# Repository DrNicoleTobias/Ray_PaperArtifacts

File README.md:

# Ray Sensor Documentation Notes

Ray is a batteryless, doorframe/passageway-mounted room-level occupancy monitoring sensor that uses changes in indoor ambient light reflections to detect people entering and exiting a room or hallway and estimate their direction of travel.

<table style="width: 100%; border-collapse: collapse;">
  <tr>
    <td style="width: 100%; text-align: center;">
      
      <br>
      <strong>Ray Use Scenario/Concept</strong>
    </td>
  </tr>
</table>

In this document, we provide the abstract of the work with highlights from our experiments, comments for the JSys reviewers, a layout of the folder/file structure, and instructions on how to build a Ray sensor and set it and a base station up for deployment.

# Abstract
Room-level occupancy-tracking systems enable intelligent control of building functions like air conditioning and power delivery to adapt to the needs of their occupants. Unfortunately, existing occupancy-tracking systems are bulky, have short battery lifetimes, are not privacy-preserving, or only provide coarse-grain occupancy information. Furthermore, retrofitting existing infrastructure with wired sensors is prohibitively expensive.

In this paper, we present Ray, a batteryless, doorframe/passageway-mounted room-level occupancy monitoring sensor that uses changes in indoor ambient light reflections to detect people entering and exiting a room or hallway and estimate direction of travel. We evaluated Ray in mixed lighting conditions on both sides of the doorway in an office-style setting, using subjects with a wide variety of physical characteristics. We conducted 881 controlled experiments in 7 doorways with 9 individuals and achieved a total detection accuracy of 100% and movement direction accuracy averaging 96.4%. Furthermore, we deployed Ray sensors for 64 days in 5 locations, comparing them with a commercial batteryless occupancy sensor. Ray outperformed the commercial sensor, particularly where traffic is moderate to heavy. Ray demonstrates that ambient light reflections provide both a promising low-cost, long-term sustainable option for monitoring how people use buildings and an exciting new research direction for batteryless computing.

# Artifact Evaluation - For JSys Reviewers
The artifacts associated with this paper consist of both hardware and software for building a functioning deployment of the Ray sensor.

We are including the custom PCB designs, Bill of Materials, and 3D prototype housing files used to create a Ray sensor. PDFs of the schematic and Design files are also included for reviewer convenience. Software for training and the firmware that runs the Ray sensor and base station are also provided. Documentation includes how to build, set up, tune, train, and deploy a Ray sensor as well as how to set up a base station for receiving the sensor data.

As the claims of this work are of the effectiveness of our custom Ray sensor, it is hard to automate items for testing and evaluation without actually having a physical sensor built, trained, and deployed for reviewers to test. After speaking with the chair of the Artifact Evaluation Board, we determined the best way to demonstrate the usability and reproducibility of this work is by providing the design files (raw and as PDFs for convenience), and making several demonstration videos to show the system working in controlled scenarios, in the presence of confounding cases, and when comparing to a commercial occupancy sensor. We hope they allow enough insight to judge the effectiveness, claims, and reproducibility of the work as it is hard to exactly recreate some of these experiments as they were gathered from live individuals walking through passageways.

# Folder/File Layout
This repo stores code, hardware files, and other technical documents for the project. Subdirectories are described below:

## Hardware
This folder contains all of the custom PCB Eagle design files (PDFs of the schematic and board design files are also included for reviewer convenience), Bill of Materials (BOM), and 3D prototype housing/enclosures files used to create a Ray sensor.

## Review_Material
This folder contains some of the additional artifact information for the working sensor including a Video Demo (.mp4) and a sampling of the data collected from both the controlled and uncontrolled experiments of the paper.  The Video Demo showcases the Ray sensor operating during a range of activities. These include people walking through doorways under the sensor, pass-by events where a person walks near the sensor but does not pass under it, and confounding cases like lingering and many people walking in a tight group. We also demonstrate in the video a comparison between the  sensor and the commercially available EnOcean sensor (a batteryless PIR-based occupancy sensor), showing that Ray is able to more accurately estimate the number of people during higher traffic conditions. 

Due to the nature of this project, much of the data gathering and ground truth labeling required manual intervention and processing to account for the amount of corner cases and fuzzy timing between two different sensors and ground truth.  A sampling of the manual data gathering for the controlled and uncontrolled experiments has been provided and the resulting excel files for the uncontrolled experiments are provided for review.  There are no scripts to run, table data for the uncontrolled experiments (Tables 5 and 6) came directly from excel formulas in the excel files for each location.

## Software
All software provided is either C code compiled and run on the MSP430FR5994 chips used for our sensor and base station or Python3 scripting code that is processed on a base station or laptop. Because there are variations in component quality and in doorway and lighting conditions, users want to train the classifier model on data more closely related to the test environment to improve accuracy. In that event, The following subfolders contain the code needed to gather the raw features from a Ray sensor (0_Get_Features) and train a new decision tree classifier model using those features (1_Train_Model). Once trained, the model will need to be manually implemented in the experiment code subfolders 2_Controlled_Studies and 3_Uncontrolled_Studies (specific locations to change are mentioned in those folders' ReadMe documentation.

### 0_Get_Features
This folder contains the firmware for both the Ray sensor and for a base station for gathering raw training data. The data gathered by the base station and sensor firmware here is intended for training a supervised classification model, in our case a decision tree model. This model should capture directional information from many individual events of common in and out events and can also include some additional example training data for some confounding, yet common, cases such as pass-by events. Have sample subjects walk in and out in a controlled manner to capture what the raw features from the sensor look like under local lighting conditions and environment. Collect this data using what is received at the base station and the result for that data that you wish to train with in a CSV file for use in training the model in the next step.

### 1_Train_Model
This folder contains a Python script called makedecisions.py that will use the CSV file of data gathered from the 0_Get_Features scripts/code in order to train a new decision tree to update the models for testing or real world deployment.

### 2_Controlled_Studies
This folder contains the firmware for both the Ray sensor and for a base station to receive packets from a Ray Sensor using the CC1101 Radio with a MSP430FR994 LaunchPad where the Ray Sensor sends a single packet for individual controlled events.

### 3_Uncontrolled_Studies
This folder contains the firmware for both the Ray sensor and for a base station to receive full packets from a deployed Ray Sensor using the CC1101 Radio with a MSP430FR994 LaunchPad where the Ray Sensor to send complete packets containing a sequence of 5 events, an estimate of their time between events, heartbeats in the absence of activity for 2 minutes, and history of the last two packets sent for redundancy.

# Building a Ray Sensor

In this section, we describe the steps it takes to build a physical Ray Sensor for deployment.

<table style="width: 150%; border-collapse: collapse;">
  <tr>
    <td style="width: 50%; text-align: center;">
      
      <br>
      <strong>Ray PCB Close Up</strong>
    </td>
    <td style="width: 100%; text-align: center;">
      
      <br>
      <strong>Ray Full Sensor</strong>
    </td>
  </tr>
</table>

## Housing/Enclosure, Parts, and Assembly
Our prototype hardware integrates a modular custom printed circuit board (PCB) housed in a 3D-printed plastic enclosure, four solar panels, and a TI CC1101 radio.

### Custom PCB
The PCB for the Ray sensor consists of three modular parts: a Solar_Module, a MCU_Module, and a Radio_Module. All design files for these modules and the Bill of Materials for all necessary PCB components can be found in the Hardware/PCB_Designs/ folder. Boards can be fabricated at many places online, such as OSHpark etc, and the components can be populated by hand or by a manufacturer as well. Design files can be viewed directly by a program like Eagle, but PDFs have been made available for convenience of viewing. The Solar_Module attaches to the MCU_Module and the MCU_Module attaches to the Radio_Module.

### 3D Enclosure
The 3D printed mounting system is made of PLA plastic and contains the PCB, solar cells, and necessary wiring connecting them. Enclosure designs to house the PCB and attach the solar panels to can be found in Hardware/3D_Enclosure/PCB_Housing_and_20_DegBody_Assembly.stl with a second file Hardware/3D_Enclosure/PCB_Housing_Cap.stl to make a cap to cover the PCB during deployment. The enclosure provides a nesting place for the solar cells, which angles the solar cell slots such that two of the four of the solar cells are pointed toward the entry, while the rest are pointed toward the exit.

### Connecting Solar Panels
Four solar panels need to be attached to the enclosure, where they will be divided into two sets of two panels each, one facing inward (the direction the radio antenna is pointing) and one set facing outward. The inward set of solar panels are connected in series and connected to the SOLAR1 terminal of the Solar Module PCB. The outward facing panels are also connected in series and then added to the SOLAR2 terminal.

### Tune the Detectors
Ray uses a detection circuit to determine when to wake up the microcontroller to assess the possible event. The detector circuitry is tunable using trim potentiometers (trim pots) pre-installation in deployment. Testers may find that, depending on the lighting conditions of a particular doorway, the sensitivity of the detector circuit's trim pots may need adjusting. We found in our experiments that we did need to adjust the trim pots some for the general lighting conditions and found that they generally worked for other similar lighting conditions without needing to be readjusted for every doorway. Using a screwdriver on TM1 for monitoring SOLAR1 or TM2 for monitoring SOLAR2 from the Solar_Module PCB schematics, turning to one direction will move the detection threshold and make the detectors more sensitive while turning in the opposite direction will make them less sensitive.

### Attaching a Radio
The Ray PCB also uses a TI CC1101 radio for communication that is to be connected to the Radio_Module in Hardware/PCB_Designs/. The TI CC1101 radio board is an off-the-shelf board that we designed a plug-in for on the Radio_Module boards. For our purposes, we considered the direction the antenna was pointing to be inward when mounting the sensor for practice, but one could train and adjust the code if pointing the other direction is preferred.

### Installing on a doorway
With all the parts assembled, tuned, connected, and attached to the 3D printed enclosure, the Ray sensor can be attached to the top of a doorway/passageway frame with solar panels facing down any preferred orientation. For our experiments, we affixed the 3D enclosure to a piece of wood with magnets screwed to the other side for ease in attaching and removing the sensor on different doorway/passageway frames, as most within our office building had metal frames or structures.

## Setting up a Base Station
To receive the data packets from the Ray Sensor, you will need a MSP430FR5994 LaunchPad and another off-the-shelf CC1101 Radio.  The radio will need to be connected to the LaunchPad’s pins as follows:
```
	*MSP430FR5994*	←    *CC1101*
		VCC	←	VCC
	 	GND	←	GND
	 	P3.4	←	GDO0
	 	P3.6	←	GDO2
	 	P4.3  	←	CSN
	 	P5.0  	←	MOSI
	 	P5.1 	←	MISO
	 	P5.2  	←	SCK 
```
And as documented in the top comment of each basestation_receive.c code in the folders containing base station code. If these pins need to be modified for a particular setup, there is an /includes/pins.h file in each folder containing base station code that can be easily modified.  Once attached, the base station firmware will need to be installed to the LaunchPad simply by connecting the LaunchPad by USB to a computer with msp-gcc installed.  Navigate to the firmware folder of interest, update the makefile as suggested in that folder’s readme, and then simply run “make install” to install the firmware on the LaunchPad.   Data can be gathered by simply reading off what is sent over serial or by using a script that grabs what is coming across from the LaunchPad over serial to a database.

## Training the event classification model
### Gather Raw Feature Data
All code needed to gather features to train a new model is located in the /Software/0_Get_Features/ folder for both the base station and the sensor.  Connect the LaunchPad to install the sensors firmware using the on board programmer (requires removing some jumpers) then return the jumpers and install the base station firmware for data collection.  Attach the sensor to a doorway or passageway face down, orientated in the direction you wish to train as inward vs outward.  Gather the data sent from the sensor to the base station over the serial port from many different individual controlled events and denote the ground truth for supervised training.  Record all of this data in a CSV file that will be used to train a new decision tree model.

### Train Model
To train a new decision for a new deployable environment, the following Python3 libraries must be installed: pandas, graphviz, and scikit-learn.  Once installed, navigate to the Software/1_Train_Model/ folder and locate the makedecisions.py file.  The file will need an updated path to the CSV feature data that was collected and there are several different classifier options available to train with.  Simply run “python3 makedecisions.py” to execute that code.  A visual graph will be generated for you to assess just how the training data falls in the model.
Some sample training data is available in that folder from our experimental setup that can be run with the makedecisions.py script in its current state to test how that script works.

### Translate Decision Tree Diagram to Implementation**
Now that a tree has been generated by the makedecisions.py script and the training data gathered, it will need to be manually translated and implemented in the deployable code for evaluating_event() found in both 2_Controlled_Experiments/RaySensor/SensorControlExperiments.c and 3_Uncontrolled_Experiments/RaySensor/SensorControlExperiments.c.  The documentation in both places will reference the line numbers where that function resides.  Once implemented, the firmware can be installed/uploaded to the sensor and the sensor can be deployed.

### Installing Firmware
The Ray firmware is designed to be ultra-low power, even in active mode, and has low computational complexity, offloading the bulk of the detection to the hardware circuits. All firmware code in the Software folder basically requires the same setup in order to program either the launchpad or the Ray Sensor.
1. Change the SUPPORT_FILE_DIRECTORY in the makefile to your msp430 gcc include
   path.
2. Hook up a MSP430FR5994 LaunchPad to your computer.
3. Connect the sensor to the Programmer pins on the LaunchPad (some jumpers may need to be removed to accomplish this) and plug them in to the appropriate programming pins on the MCU_Module.
4. Use "make install" to load the program into your device.
5. Detach from the programmer and reconnect the PCB in the enclosure and the unit is ready to be deployed. (Skip steps 3 and 5 if programming a MSP430 LaunchPad for a base station)

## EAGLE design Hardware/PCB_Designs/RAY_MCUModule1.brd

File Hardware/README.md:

This folder contains all PCB hardware module files, Bill of Materials (BOM) associated with each module and the design files to 3D print a prototyping enclosure and cap/cover for the finished sensor PCB.

# PCB_Designs
This folder contains all of the design files for the custom Ray PCB modules (Solar, MCU, and Radio) as well as PDFs of these design files for viewers convenience.  These files were created using the AutoDesk Eagle Software.

# 3D_Enclosure
This folder is for the various 3D housing models that have been created for housing the custom PCB and solar panels for the final Ray Sensor.  

**BOM.xlsx**
This is the Bill of Materials that lists the parts/components used for each of the custom PCB modules (arranged by tabs).

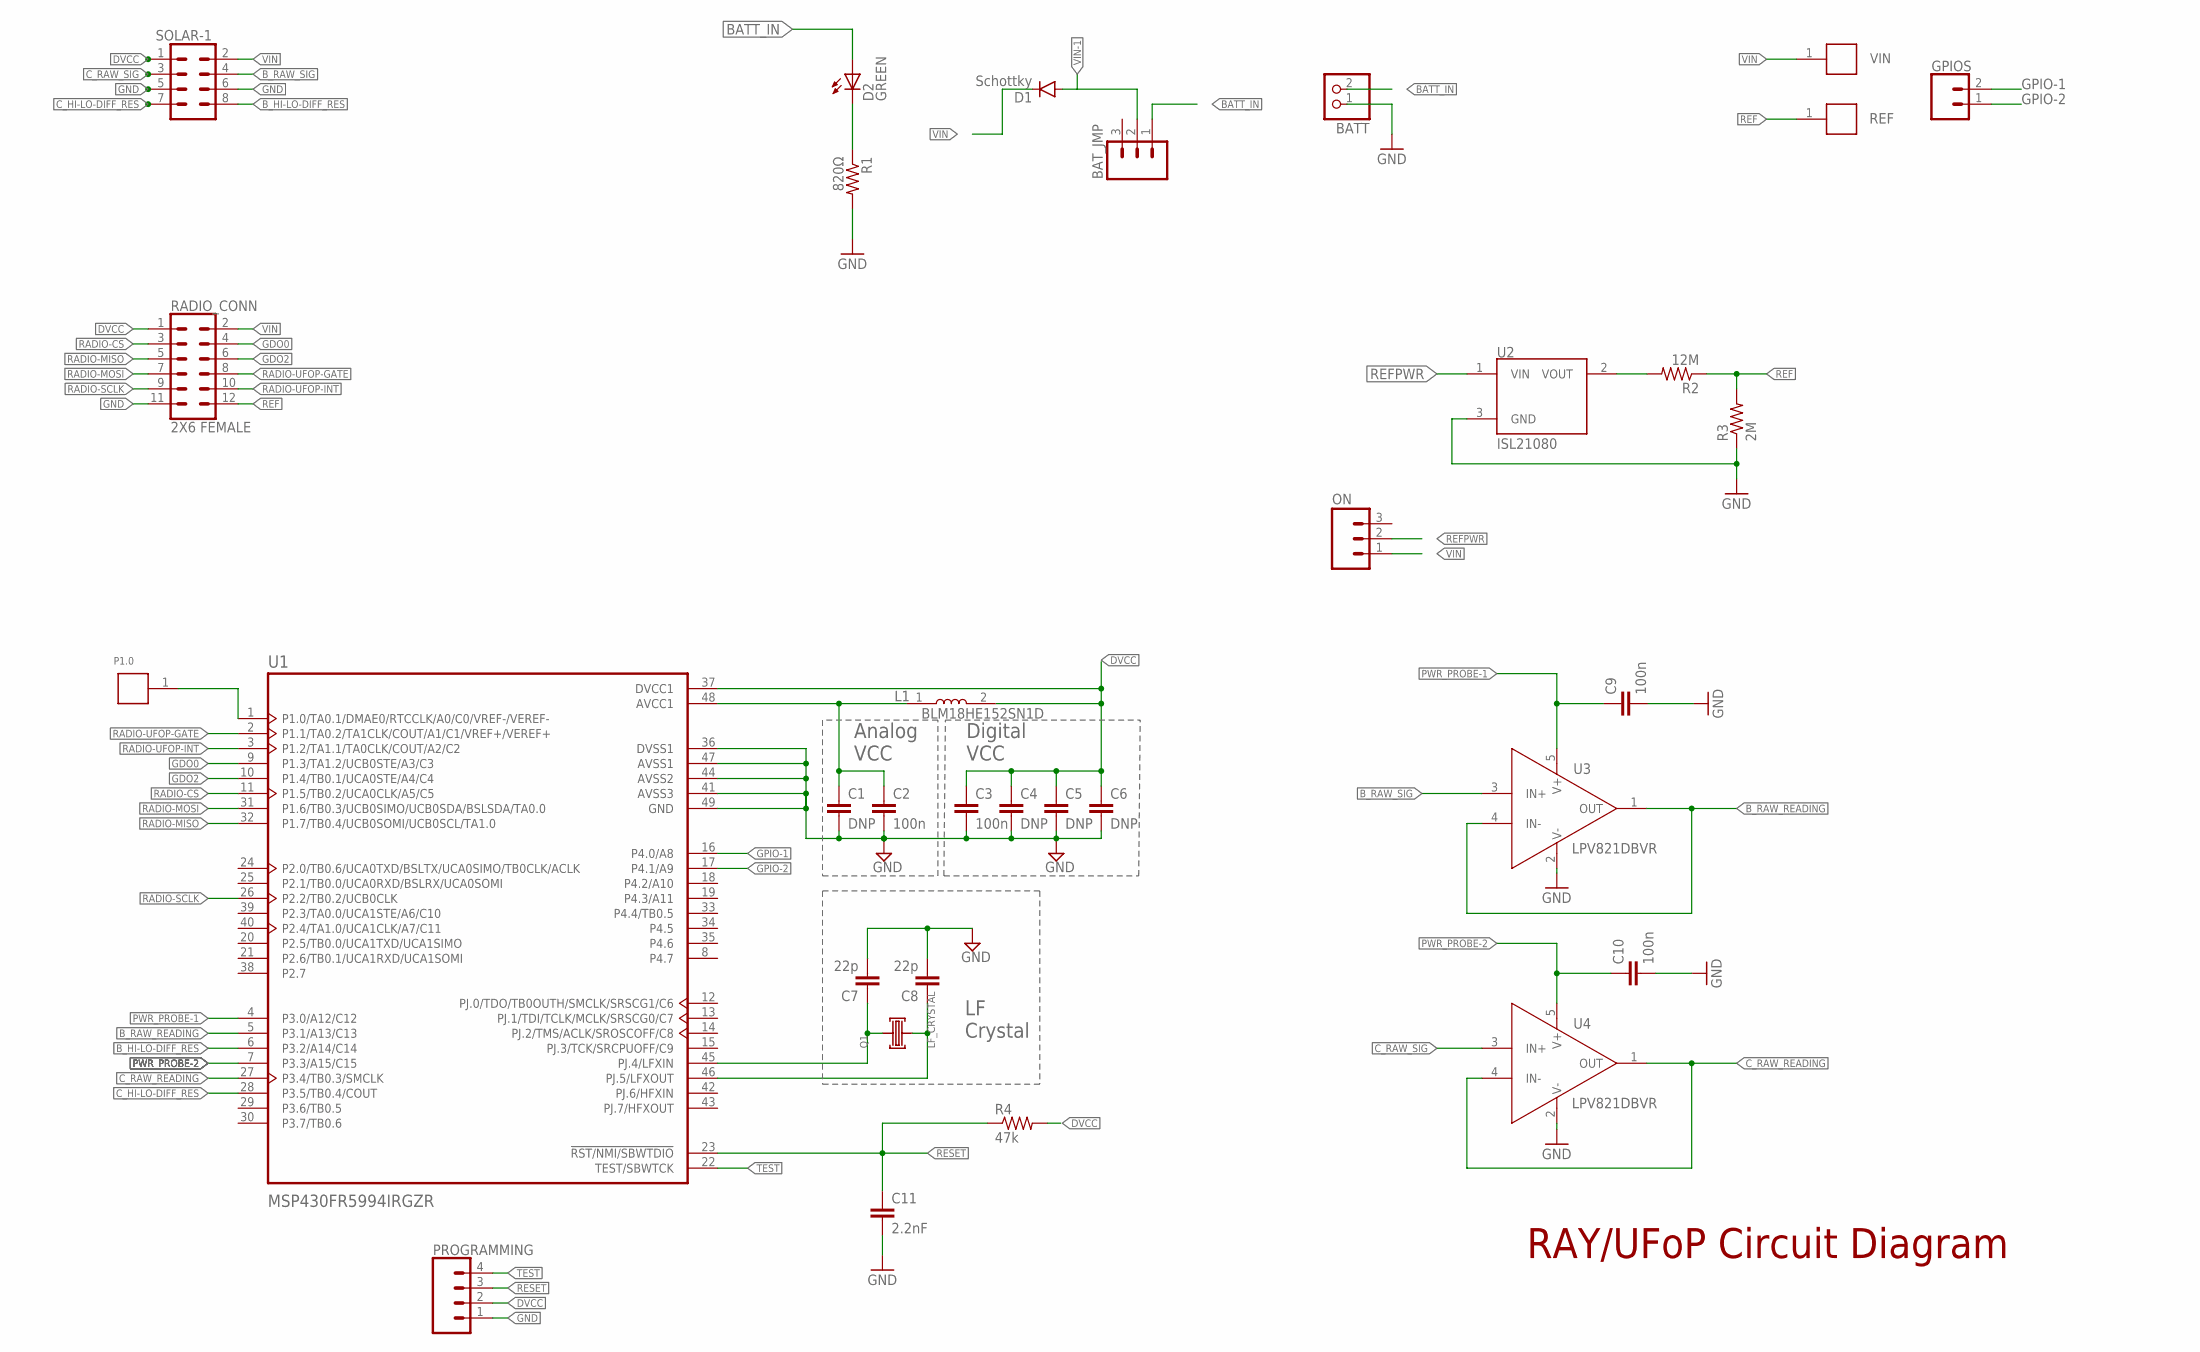
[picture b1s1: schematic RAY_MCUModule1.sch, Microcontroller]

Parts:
BATT: PINHD-1X2; 1X02
BAT_JMP: M03; 1X03-1.27MM
C1, C4, C5, C6: DNP; C0603
C2, C3, C9, C10: 100n; C0603
C7, C8: 22p; C0603
C11: 2.2nF; C0603
D1: Schottky; SOD523
D2: GREEN; CHIP-LED0805
GPIOS: CONN_02; 1X02
L1: BLM18HE152SN1D; INDC1608X95
ON: M03; 1X03-1.27MM
P1.0: RCU-0C; TE_RCU-0C
PROGRAMMING: CONN_04; 1X04
Q1: LF_CRYSTAL
R1: 820Ω; 0603-RES
R2: 12M; 0603-RES; DIGIKEY 541-6.20MHCT-ND
R3: 2M; 0603-RES; DIGIKEY 311-1.00MHRCT-ND
R4: 47k; 0603-RES; DIGIKEY 311-1.00MHRCT-ND
RADIO_CONN: 2X6 FEMALE; 2X6
REF: RCU-0C; TE_RCU-0C
SOLAR-1: CONN_04X2; 2X4
U1: MSP430FR5994IRGZR; QFN50P700X700X100-49N
U2: ISL21080; SOT-23; DIGIKEY ISL21080DIH309Z-TKCT-ND
U3, U4: LPV821DBVR; SOT95P280X145-5N
VIN: RCU-0C; TE_RCU-0C

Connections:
AVCC: C1.1, C2.1, L1.1, U1.48 (AVCC1)
BATT_IN: BATT.2, BAT_JMP.1, D2.A
B_HI-LO-DIFF_RES: SOLAR-1.8, U1.6 (P3.2/A14/C14)
B_RAW_READING: U1.5 (P3.1/A13/C13), U3.1 (OUT), U3.4 (IN-)
B_RAW_SIG: SOLAR-1.4, U3.3 (IN+)
C_HI-LO-DIFF_RES: SOLAR-1.7, U1.28 (P3.5/TB0.4/COUT)
C_RAW_READING: U1.27 (P3.4/TB0.3/SMCLK), U4.1 (OUT), U4.4 (IN-)
C_RAW_SIG: SOLAR-1.3, U4.3 (IN+)
DVCC: C3.1, C4.1, C5.1, C6.1, L1.2, PROGRAMMING.2, R4.2, RADIO_CONN.1, SOLAR-1.1, U1.37 (DVCC1)
GDO0: RADIO_CONN.4, U1.9 (P1.3/TA1.2/UCB0STE/A3/C3)
GDO2: RADIO_CONN.6, U1.10 (P1.4/TB0.1/UCA0STE/A4/C4)
GND: BATT.1, C1.2, C2.2, C3.2, C4.2, C5.2, C6.2, C7.2, C8.2, C9.2, C10.2, C11.2, PROGRAMMING.1, R1.2, R3.1, RADIO_CONN.11, SOLAR-1.5, SOLAR-1.6, U1.36 (DVSS1), U1.41 (AVSS3), U1.44 (AVSS2), U1.47 (AVSS1), U1.49 (GND), U2.3 (GND), U3.2 (V-), U4.2 (V-)
GPIO-1: GPIOS.2, U1.16 (P4.0/A8)
GPIO-2: GPIOS.1, U1.17 (P4.1/A9)
unnamed: P1.0.1, U1.1 (P1.0/TA0.1/DMAE0/RTCCLK/A0/C0/VREF-/VER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)
unnamed: D2.C, R1.1
unnamed: R2.2, U2.2 (VOUT)
unnamed: C8.1, Q1.2, U1.46 (PJ.5/LFXOUT)
unnamed: C7.1, Q1.1, U1.45 (PJ.4/LFXIN)
PWR_PROBE-1: C9.1, U1.4 (P3.0/A12/C12), U3.5 (V+)
PWR_PROBE-2: C10.1, U1.7 (P3.3/A15/C15), U4.5 (V+)
RADIO-CS: RADIO_CONN.3, U1.11 (P1.5/TB0.2/UCA0CLK/A5/C5)
RADIO-MISO: RADIO_CONN.5, U1.32 (P1.7/TB0.4/UCB0SOMI/UCB0SCL/TA1.0)
RADIO-MOSI: RADIO_CONN.7, U1.31 (P1.6/TB0.3/UCB0SIMO/UCB0SDA/BSLSDA/TA0.0)
RADIO-SCLK: RADIO_CONN.9, U1.26 (P2.2/TB0.2/UCB0CLK)
RADIO-UFOP-GATE: RADIO_CONN.8, U1.2 (P1.1/TA0.2/TA1CLK/COUT/A1/C1/VREF+/VERE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)
RADIO-UFOP-INT: RADIO_CONN.10, U1.3 (P1.2/TA1.1/TA0CLK/COUT/A2/C2)
REF: R2.1, R3.2, RADIO_CONN.12, REF.1
REFPWR: ON.2, U2.1 (VIN)
RESET: C11.1, PROGRAMMING.3, R4.1, U1.23 (!RST/NMI/SBWTDIO)
TEST: PROGRAMMING.4, U1.22 (TEST/SBWTCK)
VIN: D1.C, ON.1, RADIO_CONN.2, SOLAR-1.2, VIN.1
VIN-1: BAT_JMP.2, D1.A

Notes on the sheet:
RAY/UFoP Circuit Diagram
Analog
VCC
Digital
Crystal

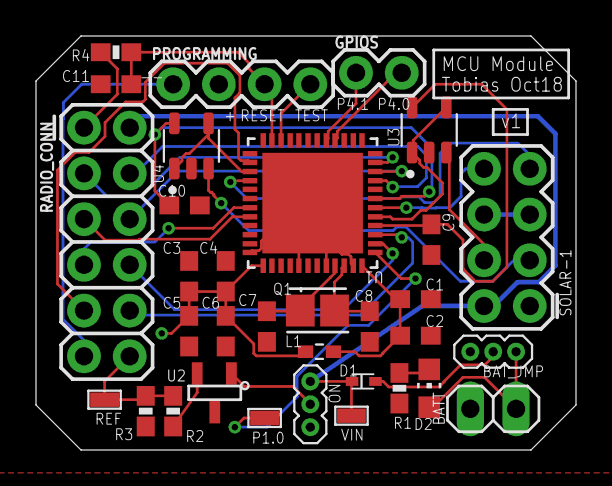
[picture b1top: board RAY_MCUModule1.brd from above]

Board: 2 copper layers, 30.0 x 23.0 mm, 33 parts (0 on the bottom side), 33 nets.

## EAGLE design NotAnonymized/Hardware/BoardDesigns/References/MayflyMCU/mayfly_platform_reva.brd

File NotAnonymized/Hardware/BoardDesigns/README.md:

This folder contains all of the various PCB design revisions and documentation over the life of this project.  
-->Note:  Documentation of Waldo hardware revisions only guaranteed complete starting with revision F.

# References
Various materials used by past hardware developers to create the base of this project's schematics

#Waldo Rev. A through #Waldo Rev. C
These folders contain past versions of the Waldo project and do not function as expected.  These are left for archival reasons as the project grows.

#Waldo Rev. D
Status:  Works kind-of.
This folder contained the closest working model of the PCB.  This PCB design, however, works as expected only when a Saleae is connected to the system at all test points as its internal resistance greatly influences the system and impacted resistor values chosen in the schematic.  

#Waldo Rev. E
Status:  Dead-end.
This folder contains an incomplete attempt at improving upon Rev. D.  Progress stalled on this attempt and ended with the graduation of a student.  

#Waldo Rev. F (NT)
Status:  Currently being developed/tested - Under construction.
This folder contains the version of Waldo's PCB design that is currently being developed.  Rather than branching from Rev. E, this was developed by a new student to the project to modify and address concerns that arose from Rev. D.  Rev. F is being developed with the assumption that a Saleae need not be attached for the system to function.  This folder contains all files and complete hardware documentation for the state of Rev. F.

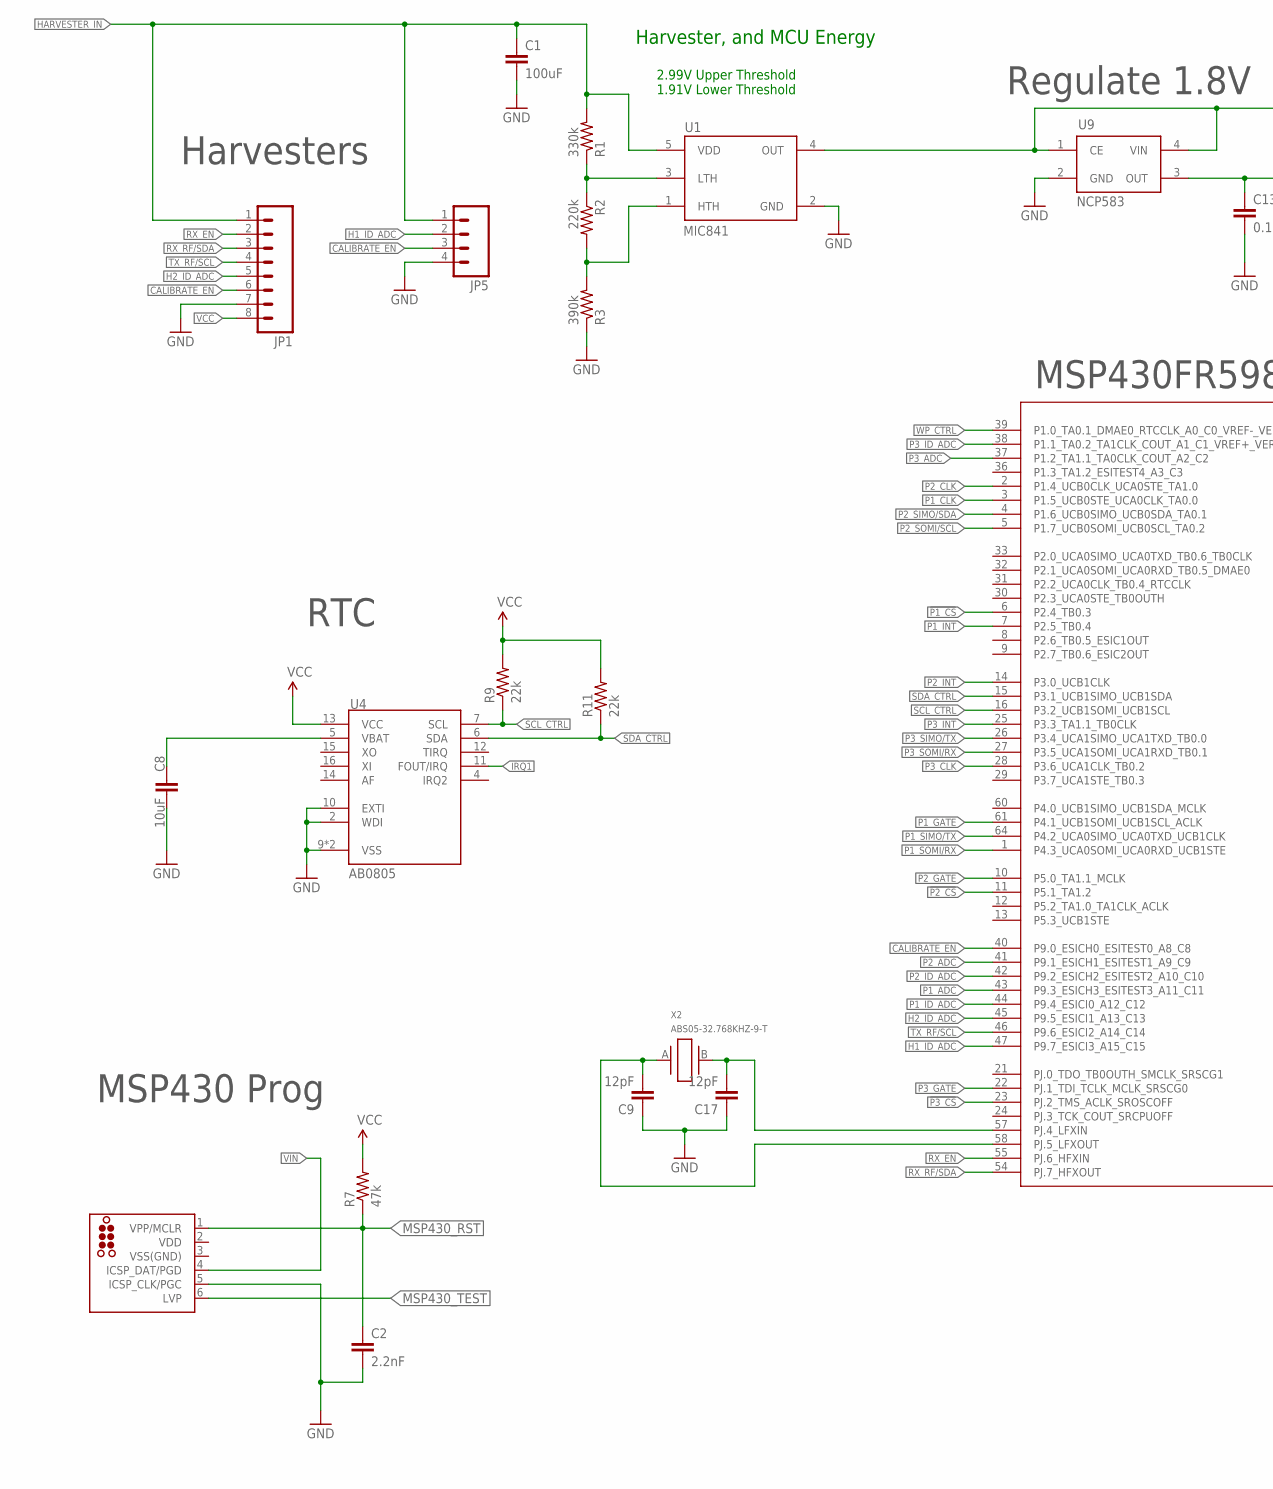
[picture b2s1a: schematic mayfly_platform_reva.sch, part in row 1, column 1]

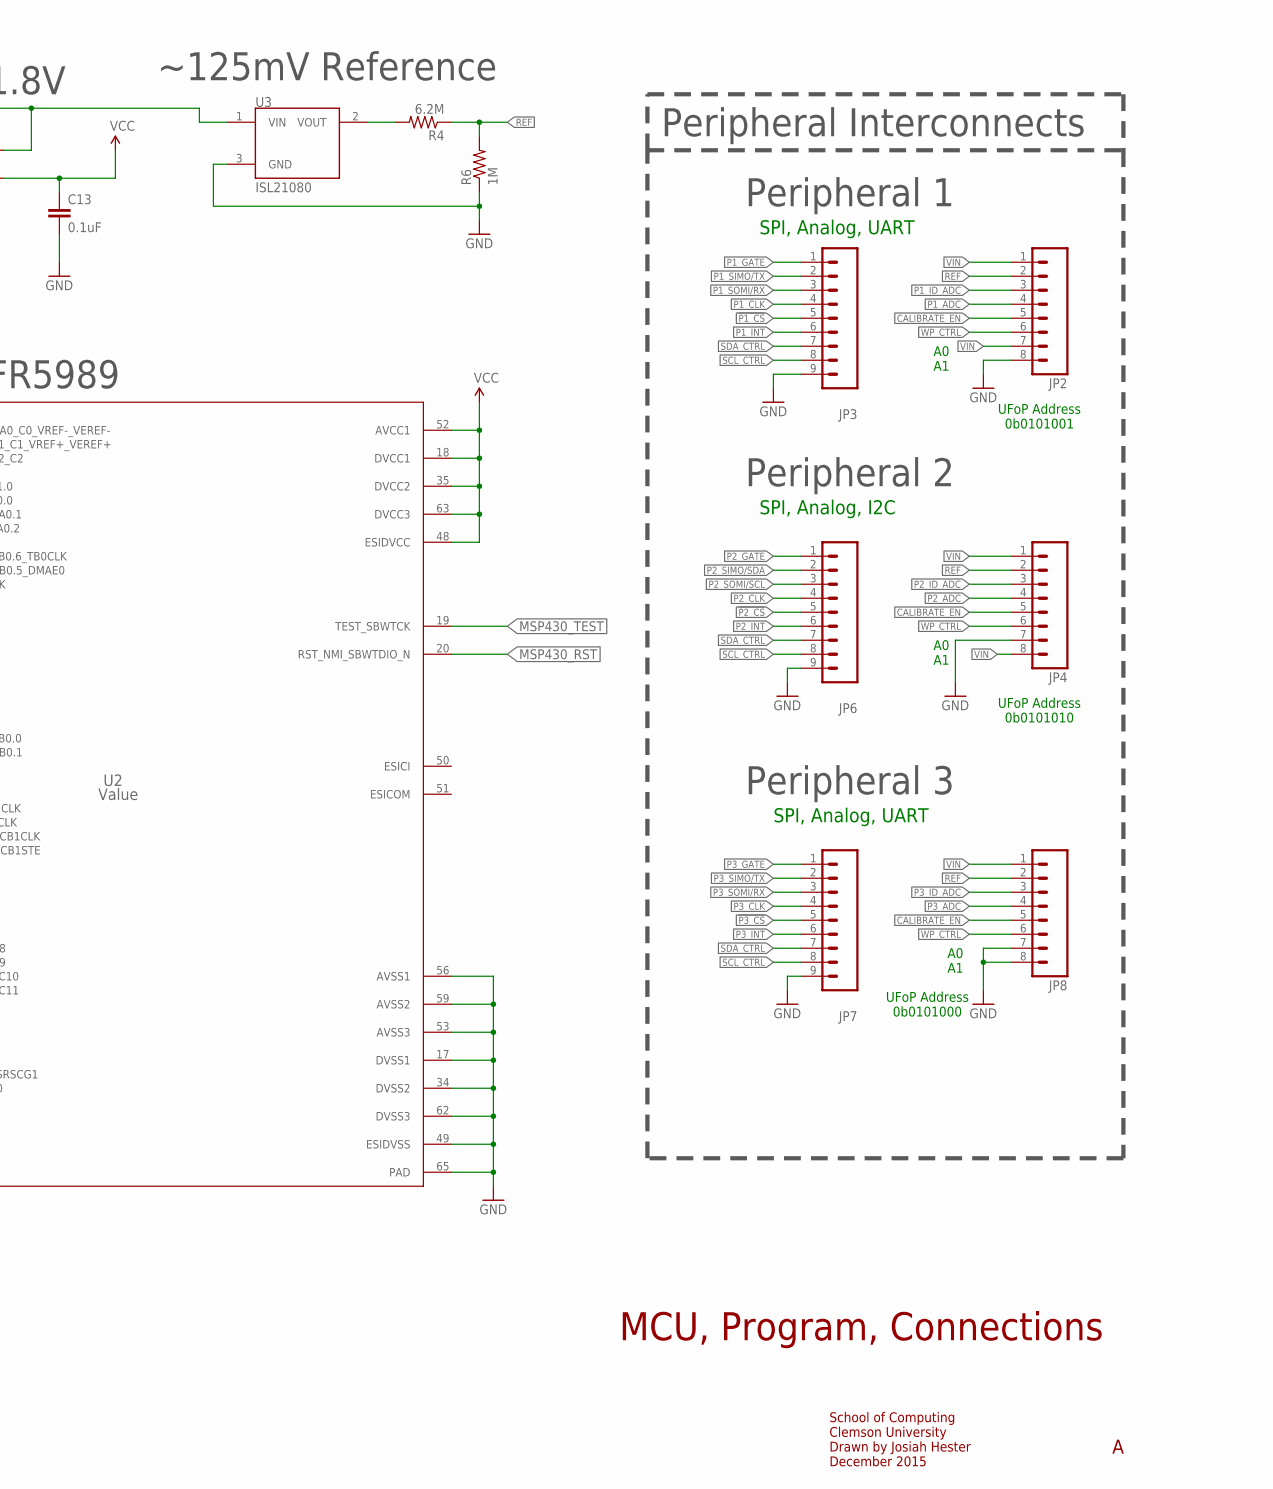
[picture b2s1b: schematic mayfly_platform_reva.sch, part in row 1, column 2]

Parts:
C1: 100uF; 1210; DIGIKEY 490-9969-1-ND
C2: 2.2nF; 0603
C8: 10uF; 0805
C9, C17: 12pF; 0603
C13: 0.1uF; 0603
J1: TC2030-MCP-NL
JP1, JP2: M081.27MM; 1X08-1.27MM; DIGIKEY S9014E-08-ND
JP3, JP6, JP7: M091.27MM; 1X09-1.27MM
JP4, JP8: M081.27MM; 1X08-1.27MM
JP5: M041.27MM; 1X04-1.27MM
R1: 330k; 0603; DIGIKEY 311-330KGRCT-ND
R2: 220k; 0603; DIGIKEY 311-220KGRCT-ND
R3: 390k; 0603; DIGIKEY 311-390KGRCT-ND
R4: 6.2M; 0603; DIGIKEY 541-6.20MHCT-ND
R6: 1M; 0603; DIGIKEY 311-1.00MHRCT-ND
R7: 47k; 0603
R9, R11: 22k; 0603
U1: MIC841; SC70-5; DIGIKEY 576-2923-1-ND
U2: Value; RGC0064B; DIGIKEY 296-42031-1-ND
U3: ISL21080; SOT-23; DIGIKEY ISL21080DIH309Z-TKCT-ND
U4: AB0805; QFN16
U9: NCP583; SC82-AB_1PRIMARY; DIGIKEY NCP583SQ18T1GOSCT-ND
X2: ABS05-32.768KHZ-9-T; ABS05

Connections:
!P1_CS: JP3.5, U2.6 (P2.4_TB0.3)
!P2_CS: JP6.5, U2.11 (P5.1_TA1.2)
!P3_CS: JP7.5, U2.23 (PJ.2_TMS_ACLK_SROSCOFF)
CALIBRATE_EN: JP1.6, JP2.5, JP4.5, JP5.3, JP8.5, U2.40 (P9.0_ESICH0_ESITEST0_A8_C8)
GND: C1.2, C2.2, C8.2, C9.1, C13.2, C17.1, J1.5 (ICSP_CLK/PGC), JP1.7, JP2.8, JP3.9, JP4.7, JP5.4, JP6.9, JP7.9, JP8.7, JP8.8, R3.1, R6.1, U1.2 (GND), U2.17 (DVSS1), U2.34 (DVSS2), U2.49 (ESIDVSS), U2.53 (AVSS3), U2.56 (AVSS1), U2.59 (AVSS2), U2.62 (DVSS3), U2.65 (PAD), U3.3 (GND), U4.2 (WDI), U4.9 (VSS), U4.10 (EXTI), U4.TH (VSS), U9.2 (GND)
H1_ID_ADC: JP5.2, U2.47 (P9.7_ESICI3_A15_C15)
H2_ID_ADC: JP1.5, U2.45 (P9.5_ESICI1_A13_C13)
HARVESTER_IN: C1.1, JP1.1, JP5.1, R1.2, U1.5 (VDD)
IRQ1: U4.11 (FOUT/IRQ)
MSP430_RST: C2.1, J1.1 (VPP/MCLR), R7.1, U2.20 (RST_NMI_SBWTDIO_N)
MSP430_TEST: J1.6 (LVP), U2.19 (TEST_SBWTCK)
unnamed: R1.1, R2.1, U1.3 (LTH)
unnamed: R4.2, U3.2 (VOUT)
unnamed: R2.2, R3.2, U1.1 (HTH)
unnamed: C17.2, U2.57 (PJ.4_LFXIN), X2.B (2)
unnamed: C9.2, U2.58 (PJ.5_LFXOUT), X2.A (1)
unnamed: C8.1, U4.5 (VBAT)
P1_ADC: JP2.4, U2.43 (P9.3_ESICH3_ESITEST3_A11_C11)
P1_CLK: JP3.4, U2.3 (P1.5_UCB0STE_UCA0CLK_TA0.0)
P1_GATE: JP3.1, U2.61 (P4.1_UCB1SOMI_UCB1SCL_ACLK)
P1_ID_ADC: JP2.3, U2.44 (P9.4_ESICI0_A12_C12)
P1_INT: JP3.6, U2.7 (P2.5_TB0.4)
P1_SIMO/TX: JP3.2, U2.64 (P4.2_UCA0SIMO_UCA0TXD_UCB1CLK)
P1_SOMI/RX: JP3.3, U2.1 (P4.3_UCA0SOMI_UCA0RXD_UCB1STE)
P2_ADC: JP4.4, U2.41 (P9.1_ESICH1_ESITEST1_A9_C9)
P2_CLK: JP6.4, U2.2 (P1.4_UCB0CLK_UCA0STE_TA1.0)
P2_GATE: JP6.1, U2.10 (P5.0_TA1.1_MCLK)
P2_ID_ADC: JP4.3, U2.42 (P9.2_ESICH2_ESITEST2_A10_C10)
P2_INT: JP6.6, U2.14 (P3.0_UCB1CLK)
P2_SIMO/SDA: JP6.2, U2.4 (P1.6_UCB0SIMO_UCB0SDA_TA0.1)
P2_SOMI/SCL: JP6.3, U2.5 (P1.7_UCB0SOMI_UCB0SCL_TA0.2)
P3_ADC: JP8.4, U2.37 (P1.2_TA1.1_TA0CLK_COUT_A2_C2)
P3_CLK: JP7.4, U2.28 (P3.6_UCA1CLK_TB0.2)
P3_GATE: JP7.1, U2.22 (PJ.1_TDI_TCLK_MCLK_SRSCG0)
P3_ID_ADC: JP8.3, U2.38 (P1.1_TA0.2_TA1CLK_COUT_A1_C1_VREF+_VERE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)
P3_INT: JP7.6, U2.25 (P3.3_TA1.1_TB0CLK)
P3_SIMO/TX: JP7.2, U2.26 (P3.4_UCA1SIMO_UCA1TXD_TB0.0)
P3_SOMI/RX: JP7.3, U2.27 (P3.5_UCA1SOMI_UCA1RXD_TB0.1)
REF: JP2.2, JP4.2, JP8.2, R4.1, R6.2
RX_EN: JP1.2, U2.55 (PJ.6_HFXIN)
RX_RF/SDA: JP1.3, U2.54 (PJ.7_HFXOUT)
SCL_CTRL: JP3.8, JP6.8, JP7.8, R9.1, U2.16 (P3.2_UCB1SOMI_UCB1SCL), U4.7 (SCL)
SDA_CTRL: JP3.7, JP6.7, JP7.7, R11.1, U2.15 (P3.1_UCB1SIMO_UCB1SDA), U4.6 (SDA)
TX_RF/SCL: JP1.4, U2.46 (P9.6_ESICI2_A14_C14)
VCC: C13.1, JP1.8, R7.2, R9.2, R11.2, U2.18 (DVCC1), U2.35 (DVCC2), U2.48 (ESIDVCC), U2.52 (AVCC1), U2.63 (DVCC3), U4.13 (VCC), U9.3 (OUT)
VDD: J1.2 (VDD)
VIN: J1.4 (ICSP_DAT/PGD), JP2.1, JP2.7, JP4.1, JP4.8, JP8.1, U1.4 (OUT), U3.1 (VIN), U9.1 (CE), U9.4 (VIN)
VSS(GND): J1.3 (VSS(GND))
WP_CTRL: JP2.6, JP4.6, JP8.6, U2.39 (P1.0_TA0.1_DMAE0_RTCCLK_A0_C0_VREF-_VER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)

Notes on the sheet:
MCU, Program, Connections
School of Computing Clemson University Drawn by Josiah Hester December 2015
MSP430FR5989
Regulate 1.8V
MSP430 Prog
RTC
2.99V Upper Threshold 1.91V Lower Threshold
Harvester, and MCU Energy
~125mV Reference
Peripheral 1
Peripheral 2
Peripheral 3
Harvesters
SPI, Analog, I2C
SPI, Analog, UART
Peripheral Interconnects
UFoP Address 0b0101000
UFoP Address 0b0101001
UFoP Address 0b0101010
A0 A1

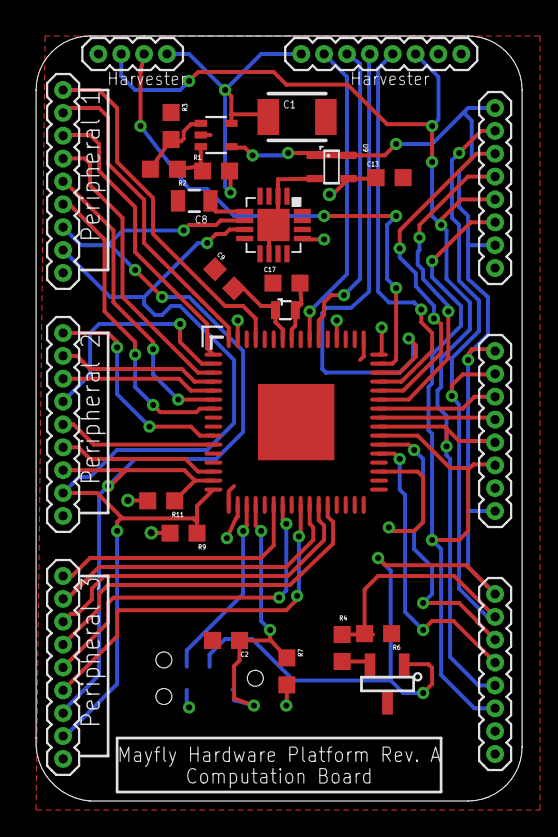
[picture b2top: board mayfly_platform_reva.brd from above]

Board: 2 copper layers, 27.0 x 42.5 mm, 29 parts (1 on the bottom side), 46 nets.

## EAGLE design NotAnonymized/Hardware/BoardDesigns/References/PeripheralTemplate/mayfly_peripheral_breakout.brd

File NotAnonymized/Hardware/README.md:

This folder contains all PCB hardware file versions, which include images, documentation of changes, and BOMs associated with those versions.

# BoardDesigns
This folder contains all of the various PCB design revisions and documentation over the life of this project.  

# Enclosures3D
This folder is for the various 3D housing models that have been created for use in the Waldo project over the various revisions.

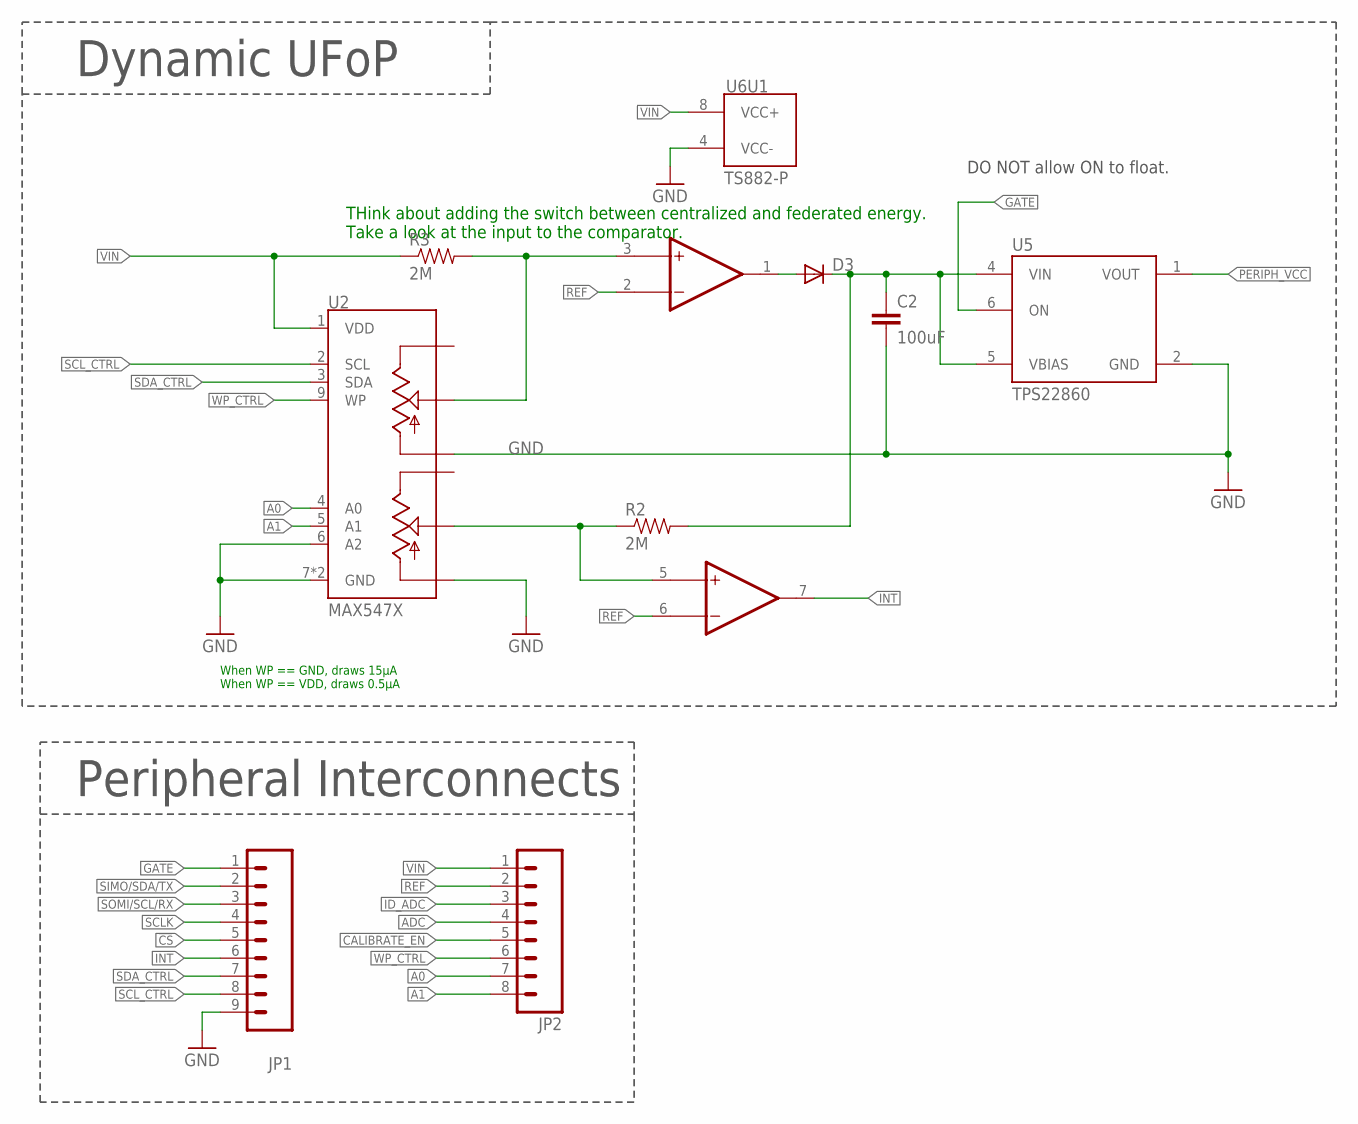
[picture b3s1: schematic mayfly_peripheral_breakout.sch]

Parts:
C2: 100uF; 1210; DIGIKEY 490-9969-1-ND
D3: DIODESOD; SOD-323
JP1: M09LOCK; 1X09_LOCK
JP2: M08LOCK; 1X08_LOCK
R2: 2M; 0603; DIGIKEY 311-2.00MHRCT-ND
R3: 2M; 0603
U2: MAX547X; QFN16; DIGIKEY MAX5479ETE+-ND
U5: TPS22860; TSOT23-6
U6: TS882-P; UDFN8; DIGIKEY 497-14073-1-ND

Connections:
!CS: JP1.5
A0: JP2.7, U2.4 (A0)
A1: JP2.8, U2.5 (A1)
ADC: JP2.4
CALIBRATE_EN: JP2.5
GATE: JP1.1, U5.6 (ON)
GND: C2.2, JP1.9, U2.6 (A2), U2.7 (GND), U2.10 (LB), U2.13 (LA), U2.TH (GND), U5.2 (GND), U6.4 (VCC-)
ID_ADC: JP2.3
INT: JP1.6, U6.7 (OUT1)
unnamed: D3.2 (A), U6.1 (OUT1)
unnamed: C2.1, D3.1 (C), R2.2, U5.4 (VIN), U5.5 (VBIAS)
unnamed: R3.2, U2.14 (WA), U6.3 (IN1+)
unnamed: R2.1, U2.11 (WB), U6.5 (IN1+)
PERIPH_VCC: U5.1 (VOUT)
REF: JP2.2, U6.2 (IN1-), U6.6 (IN1-)
SCLK: JP1.4
SCL_CTRL: JP1.8, U2.2 (SCL)
SDA_CTRL: JP1.7, U2.3 (SDA)
SIMO/SDA/TX: JP1.2
SOMI/SCL/RX: JP1.3
VIN: JP2.1, R3.1, U2.1 (VDD), U6.8 (VCC+)
WP_CTRL: JP2.6, U2.9 (WP)

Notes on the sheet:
DO NOT allow ON to float.
THink about adding the switch between centralized and federated energy. Take a look at the input to the comparator.
When WP == GND, draws 15µA When WP == VDD, draws 0.5µA
Peripheral Interconnects
Dynamic UFoP

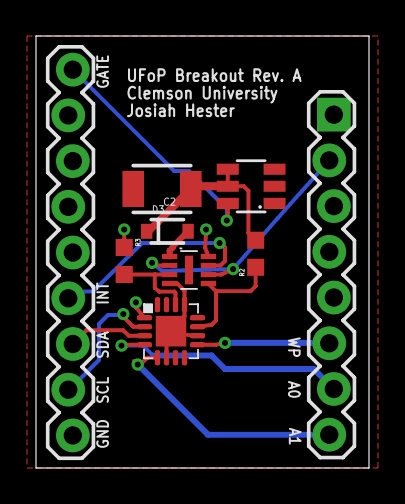
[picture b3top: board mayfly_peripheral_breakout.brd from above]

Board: 2 copper layers, 18.5 x 24.0 mm, 9 parts (0 on the bottom side), 14 nets.

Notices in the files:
parts and their libraries:
SparkFun-Connectors: Licensing: Creative Commons ShareAlike 4.0 International - https://creativecommons.org/licenses/by-sa/4.0
tag-connect_msp430: ©2009 ROFA.cz - modified and updated by Robert Darlington ‹rdarlington@gmail.com›
